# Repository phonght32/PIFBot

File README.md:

# PIFBot
  
### 1. Overview 

PIFBot is a ROS-based mobile robot for running SLAM (Simultaneous Localization and Mapping) algorithms to build a map and driving around this map. This robot is primarily equiped LiDAR, RGB-D camera and odometer sensors that makes it compatible with many SLAM methods. The PIFBot can be customized in various ways depending on how you reconstruct mechanical parts and use optional parts such as sensors and the computer to meet many different purposes. 

### 2. Requirement

#### 2.1. Ubuntu 16.04 Xenial
Ubuntu has been the primary platform for ROS. The releases is available to download from [Ubuntu home page.](https://ubuntu.com/)

#### 2.2. ROS Kinetic
This project uses ROS Kinetic that compatible with Ubuntu 16.04 (Xenial) to have better support from ROS community. Follow this [link](http://wiki.ros.org/kinetic) to see the installation instructions. 

#### 2.3. STM-IDF (STM32 Integrated Developement Framework)
[STM-IDF](https://github.com/phonght32/stm-idf) is an open source framework for STM32 that using C/C++ programming languague. The majority of the components in STM-IDF are available in [Github Repository](https://github.com/phonght32) under the MIT license. 

### 3. Mobile base control

Main controller board for PIFBot is OpenSTM32. The OpenSTM32 board is developed for ROS embedded systems to provide completely open source hardware and software. Everything about the board; Schematic, PCB Gerber, BOM and the firmware source code for PIFBot are available in [Github Repository](https://github.com/phonght32/openSTM32F4_LQFP64) and free to distribute under MIT license. 

The STM32F4 series is a main chip inside the OpenSTM32 board which is based on a very powerful ARM Cortex-M4 with Floating Point Unit (FPU). The developement environment for OpenSTM32 is wide open but STM-IDF which mentioned above is selected as main programming tool. 

OpenSTM32 provides digital and analog input/output pins that can interface with extension board or various sensors. 9-DOF IMU MPU9250 is available to make this board capable of processing complex motion fusion algorithms. OpenSTM32 features various communication interfaces: SPI, I2C, UART, I2S for other embedded devices. 

OpenSTM32 will be the best solution for implementing your embedded control design.

#### 3.1. Schematic

#### 3.2. openSTM32 Board

### 4. Hardware assembly

Differential drive which is the most common mobile robot model is applied to PIFBot. The shape of the robot is selected as circle with two driving wheels and two caster wheels. Design in this way make the robot easy to move according to control commands. 

This table shows many important size specifications of PIFBot. 

| Specification    | Dimension |
|------------------|-----------|
| Chassis diameter | 200 mm    |
| Maximum height   | 212 mm    |
| Wheel diameter   | 65 mm     |
| Axle distance    | 165 mm    |

#### 4.1. Chassis
PIFBot's chassis is made of mica. The chassis is designed in the way so that make it easy to carry optional parts as well as sensors. DXF files is available in this repository for laser cutting or CNC.

#### 4.2. Motor control and wheels
TB6560 stepper motor driver is used for controlling 42x42 mm stepper motor which working as actuator element. The PIFBot consists of two 65mm diameter fixed powered wheels mounted on the left and right side of the robot platform. Two castor wheels is used for balance and stability. 

#### 4.3. Single Board Computer
The Single Board Computer (SBC) is required to be able to install Linux ROS that provides the ability to use PIFBot's feature. There are various type of SBC, but Raspberry Pi 3 B+ is selected as main computer for PIFBot. 

#### 4.4. Controller Board
Calculating odometry data and controlling robot's motion are the essential requirements of controller board. The OpenSTM32 is designed to meet this requirements. There are also many available connectors in this board that make it suitable for various sensors or other applications. 

#### 4.5. Sensors
**RPLIDAR A1**  
360 Laser Range Finding RPLIDAR A1 is a 2D laser scanner capable of sensing 360 degrees that collects a set of data around the robot to use for SLAM (Simultaneous Localization and Mapping) and Navigation. It supportsnUSB interface and is easy to install on a PC. 

**Intel RealSense D415**  
The Intel RealSense D415 camera is a USB 3.0 device that can provide color, depth and infrared video streams. PIFBot adopts this camera to enable 3D SLAM and Navigation, and it is possible to apply various applications such as gesture recognition, object recognition and scene recognition based on 3D depth information obtained using RealSense Tecnology. 

#### 4.6. Power supply
OpenSTM32 controller board has both a 5V power and a 12V power, which are used in Raspberry Pi. DC/DC Buck Converter LM2596 is used for taking 11.1V from 3 cell lipo baterry and converting it into 5V that can power controller board and SBC.

### 5. System design

The system is seperated into two parts: ROS and base control. SBC receives data that collected from RPLIDAR A1 and Intel RealSense D415 camera to publish to ROS's topics. ROS's topics are owned by ROS Master so PC also implement publisher and subscriber to topics which contains data published from SBC. PC runs SLAM algorithms and Navigation, then publish motion commands to topic that manages robot's velocity (both angular and linear velocity). The motion command will be sent to controller board over rosserial protocol so that robot can build the map and drive around in this map. Simultaneously, controller board calculates robot's odometry data and feeds backward to ROS Server.

### 6. Result
Real-Time Appearance-Based Mapping is used for practing SLAM and Navigation. 

#### 6.1. SLAM

#### 6.2. Navigation

#### 6.3. Loop-closed detection

#### 6.4. Multi-session SLAM 

#### 6.5 Video
Follow [this link](https://youtu.be/UWhPCQyU918) to watch video on Youtube. 

#### 7. Problem
For any problems, please report to [Issues](https://github.com/phonght32/PIFBot/issues) or contact email thanhphongho1998@gmail.com

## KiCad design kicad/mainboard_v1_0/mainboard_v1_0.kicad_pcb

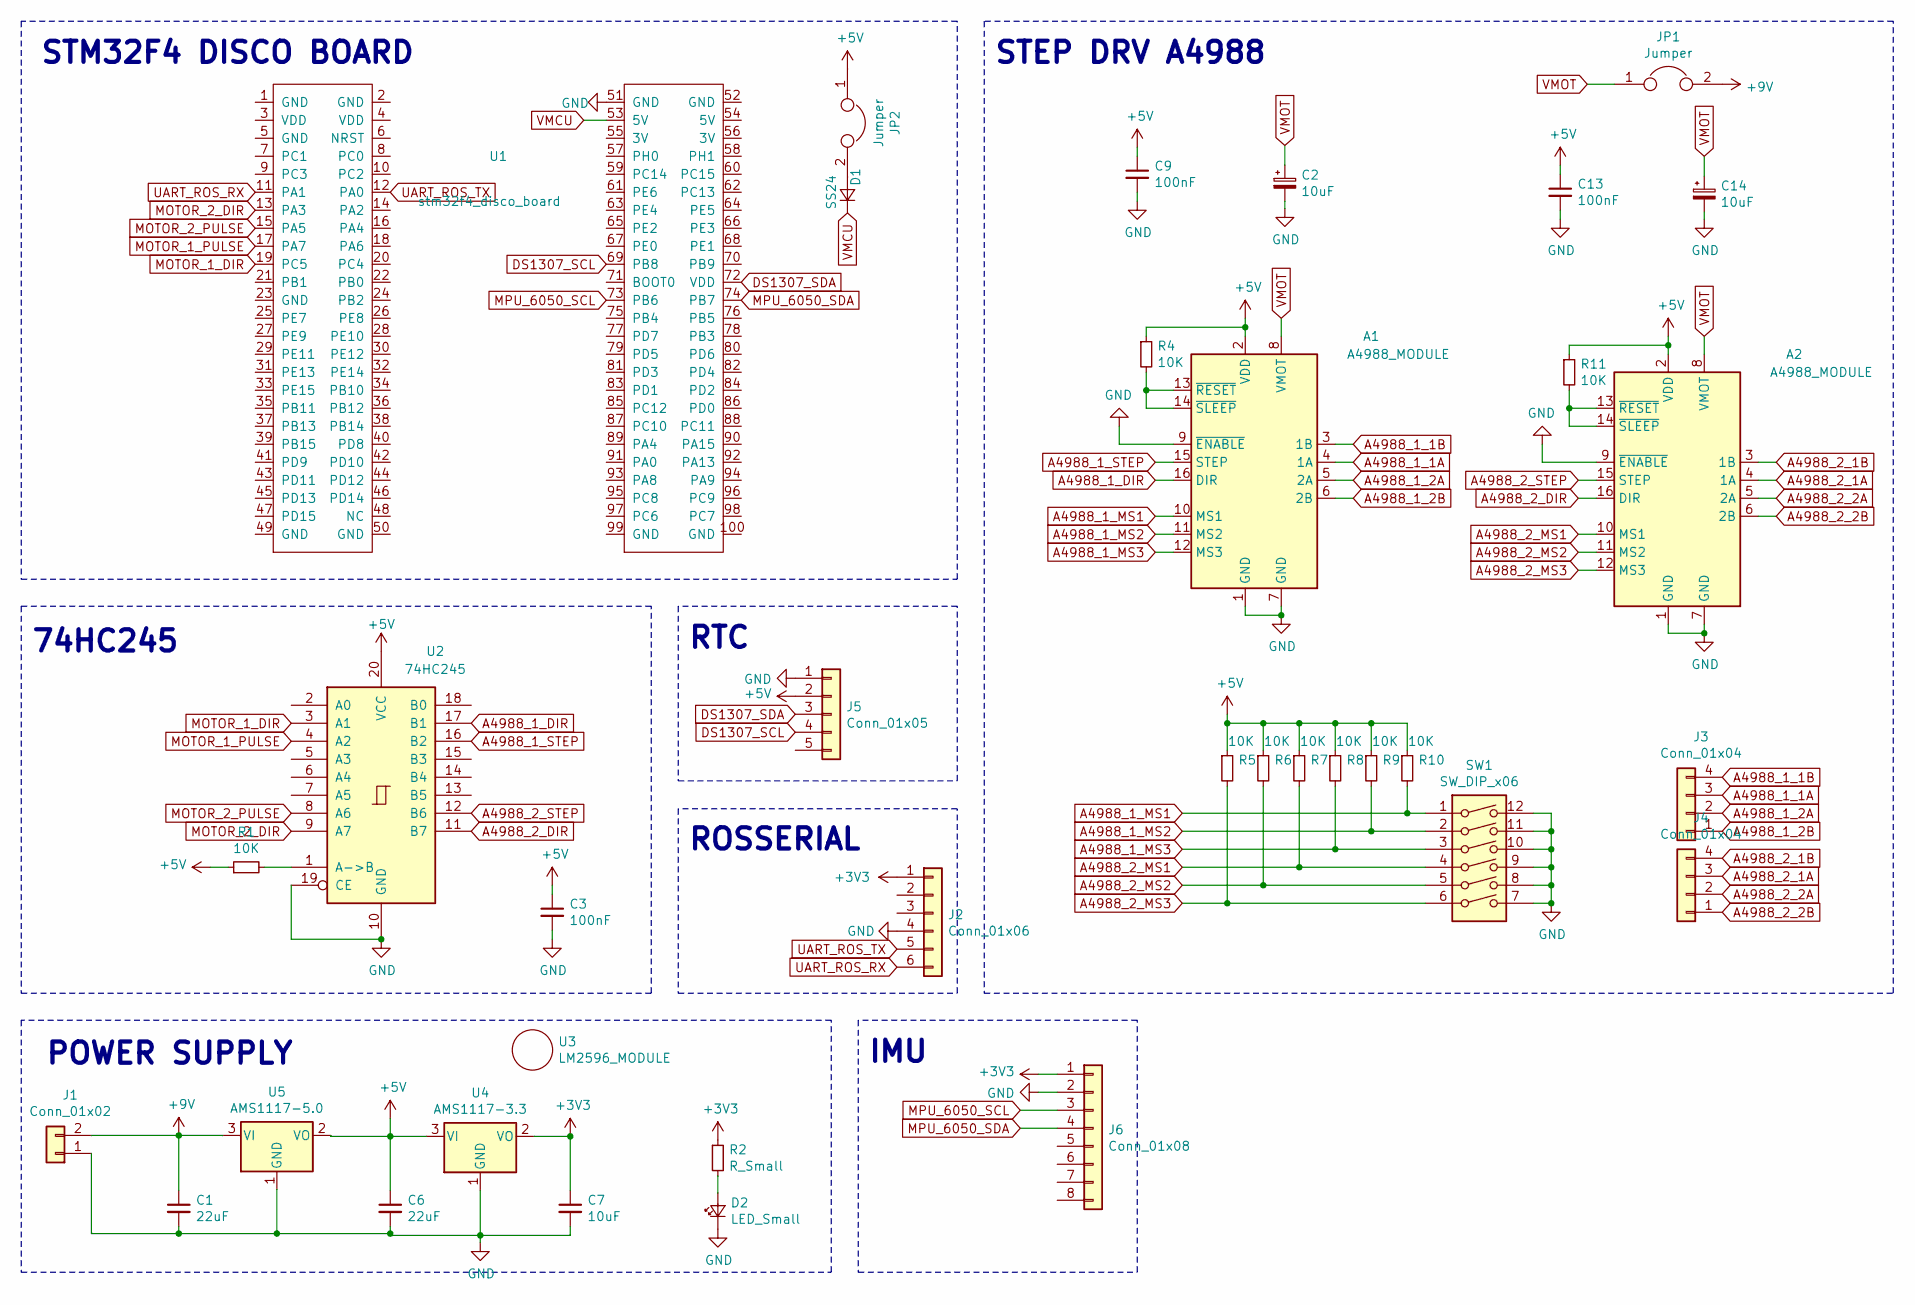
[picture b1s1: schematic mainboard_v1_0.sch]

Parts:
A1, A2: A4988_MODULE; Pololu_Breakout-16_15.2x20.3mm
C1, C6: 22uF; C_0805_2012Metric
C2, C14: 10uF; C_Radial_D8.0mm_H11.5mm_P3.50mm
C3, C9, C13: 100nF; C_0805_2012Metric
C7: 10uF; C_0805_2012Metric
D1: SS24; D_5W_P12.70mm_Horizontal
D2: LED_Small; LED_D3.0mm
J1: Conn_01x02; TerminalBlock_bornier-2_P5.08mm
J2: Conn_01x06; PinHeader_1x06_P2.54mm_Horizontal
J3, J4: Conn_01x04; PinHeader_1x04_P2.54mm_Vertical
J5: Conn_01x05; PinHeader_1x05_P2.54mm_Vertical
J6: Conn_01x08; PinHeader_1x08_P2.54mm_Vertical
JP1, JP2: Jumper; PinHeader_1x02_P2.54mm_Vertical
R1, R4, R5, R6, R7, R8, R9, R10, R11: 10K; R_Axial_DIN0207_L6.3mm_D2.5mm_P10.16mm_Horizontal
R2: R_Small; R_Axial_DIN0207_L6.3mm_D2.5mm_P10.16mm_Horizontal
SW1: SW_DIP_x06; SW_DIP_SPSTx06_Slide_9.78x17.42mm_W7.62mm_P2.54mm
U1: stm32f4_disco_board
U2: 74HC245; DIP-20_W7.62mm_LongPads
U3: LM2596_MODULE
U4: AMS1117-3.3; SOT-223-3_TabPin2
U5: AMS1117-5.0; SOT-223-3_TabPin2

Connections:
+3V3: C7.1, J2.1, J6.1, R2.1, U4.2 (VO)
+5V: A1.2 (VDD), A2.2 (VDD), C3.1, C6.1, C9.1, C13.1, J5.2, JP2.1, R1.1, R4.1, R5.1, R6.1, R7.1, R8.1, R9.1, R10.1, R11.1, U2.20 (VCC), U4.3 (VI), U5.2 (VO)
+9V: C1.1, J1.2, JP1.2, U5.3 (VI)
A4988_1_1A: A1.4 (1A), J3.3
A4988_1_1B: A1.3 (1B), J3.4
A4988_1_2A: A1.5 (2A), J3.2
A4988_1_2B: A1.6 (2B), J3.1
A4988_1_DIR: A1.16 (DIR), U2.17 (B1)
A4988_1_MS1: A1.10 (MS1), R10.2, SW1.1
A4988_1_MS2: A1.11 (MS2), R9.2, SW1.2
A4988_1_MS3: A1.12 (MS3), R8.2, SW1.3
A4988_1_STEP: A1.15 (STEP), U2.16 (B2)
A4988_2_1A: A2.4 (1A), J4.3
A4988_2_1B: A2.3 (1B), J4.4
A4988_2_2A: A2.5 (2A), J4.2
A4988_2_2B: A2.6 (2B), J4.1
A4988_2_DIR: A2.16 (DIR), U2.11 (B7)
A4988_2_MS1: A2.10 (MS1), R7.2, SW1.4
A4988_2_MS2: A2.11 (MS2), R6.2, SW1.5
A4988_2_MS3: A2.12 (MS3), R5.2, SW1.6
A4988_2_STEP: A2.15 (STEP), U2.12 (B6)
DS1307_SCL: J5.4, U1.69 (PB8)
DS1307_SDA: J5.3, U1.72 (VDD)
GND: A1.1 (GND), A1.7 (GND), A1.9 (~ENABLE), A2.1 (GND), A2.7 (GND), A2.9 (~ENABLE), C1.2, C2.2, C3.2, C6.2, C7.2, C9.2, C13.2, C14.2, D2.1 (K), J1.1, J2.4, J5.1, J6.2, SW1.7, SW1.8, SW1.9, SW1.10, SW1.11, SW1.12, U1.51 (GND), U2.10 (GND), U2.19 (CE), U4.1 (GND), U5.1 (GND)
MOTOR_1_DIR: U1.19 (PC5), U2.3 (A1)
MOTOR_1_PULSE: U1.17 (PA7), U2.4 (A2)
MOTOR_2_DIR: U1.13 (PA3), U2.9 (A7)
MOTOR_2_PULSE: U1.15 (PA5), U2.8 (A6)
MPU_6050_SCL: J6.3, U1.73 (PB6)
MPU_6050_SDA: J6.4, U1.74 (PB7)
unnamed: A1.13 (~RESET), A1.14 (~SLEEP), R4.2
unnamed: A2.13 (~RESET), A2.14 (~SLEEP), R11.2
unnamed: D1.2 (A), JP2.2
unnamed: D2.2 (A), R2.2
unnamed: R1.2, U2.1 (A->B)
UART_ROS_RX: J2.6, U1.11 (PA1)
UART_ROS_TX: J2.5, U1.12 (PA0)
VMCU: D1.1 (K), U1.53 (5V)
VMOT: A1.8 (VMOT), A2.8 (VMOT), C2.1, C14.1, JP1.1

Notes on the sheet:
STM32F4 DISCO BOARD
74HC245
POWER SUPPLY
RTC
ROSSERIAL
IMU
STEP DRV A4988

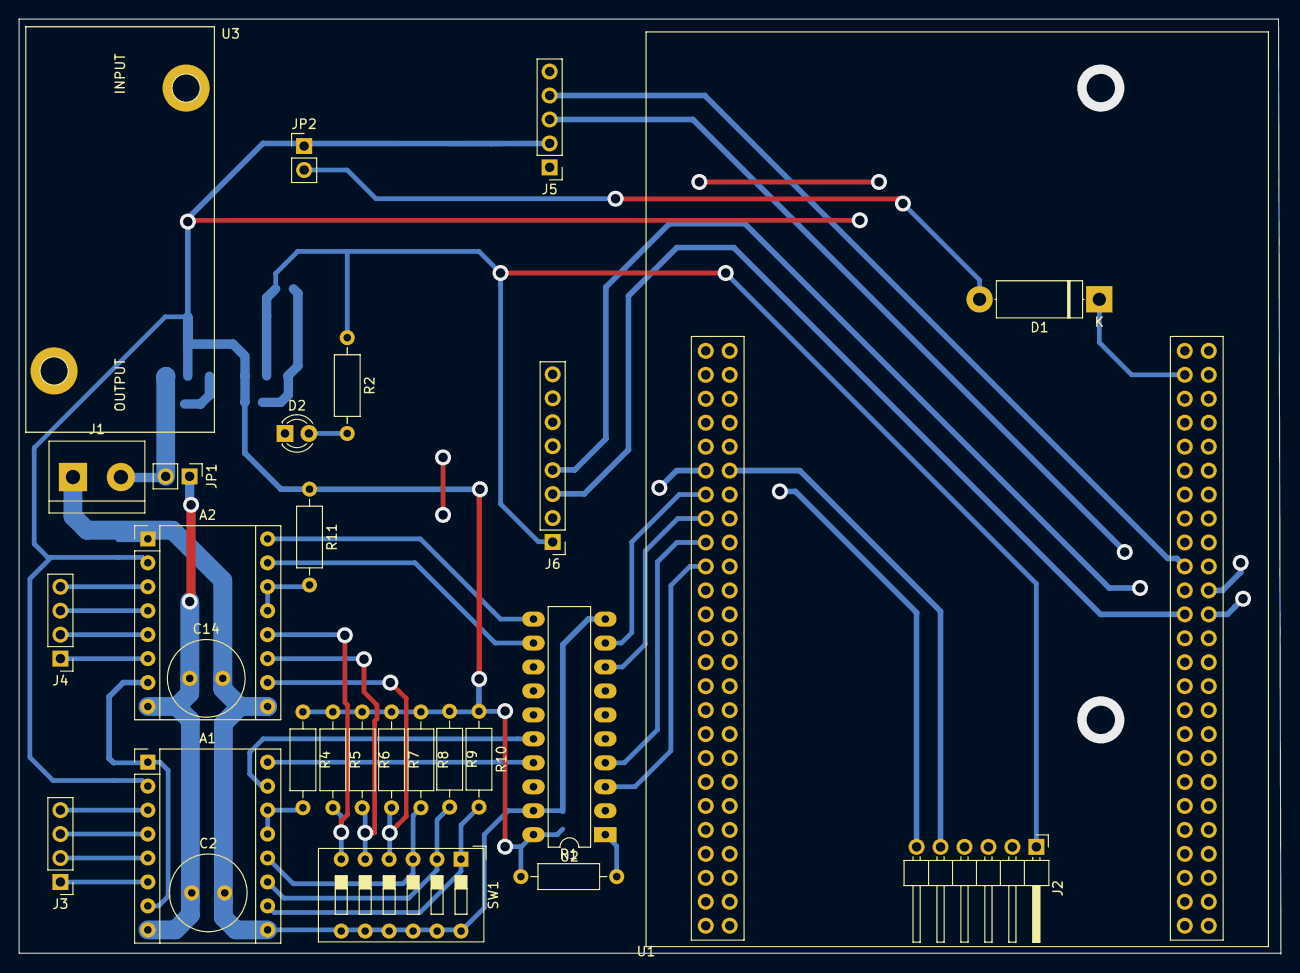
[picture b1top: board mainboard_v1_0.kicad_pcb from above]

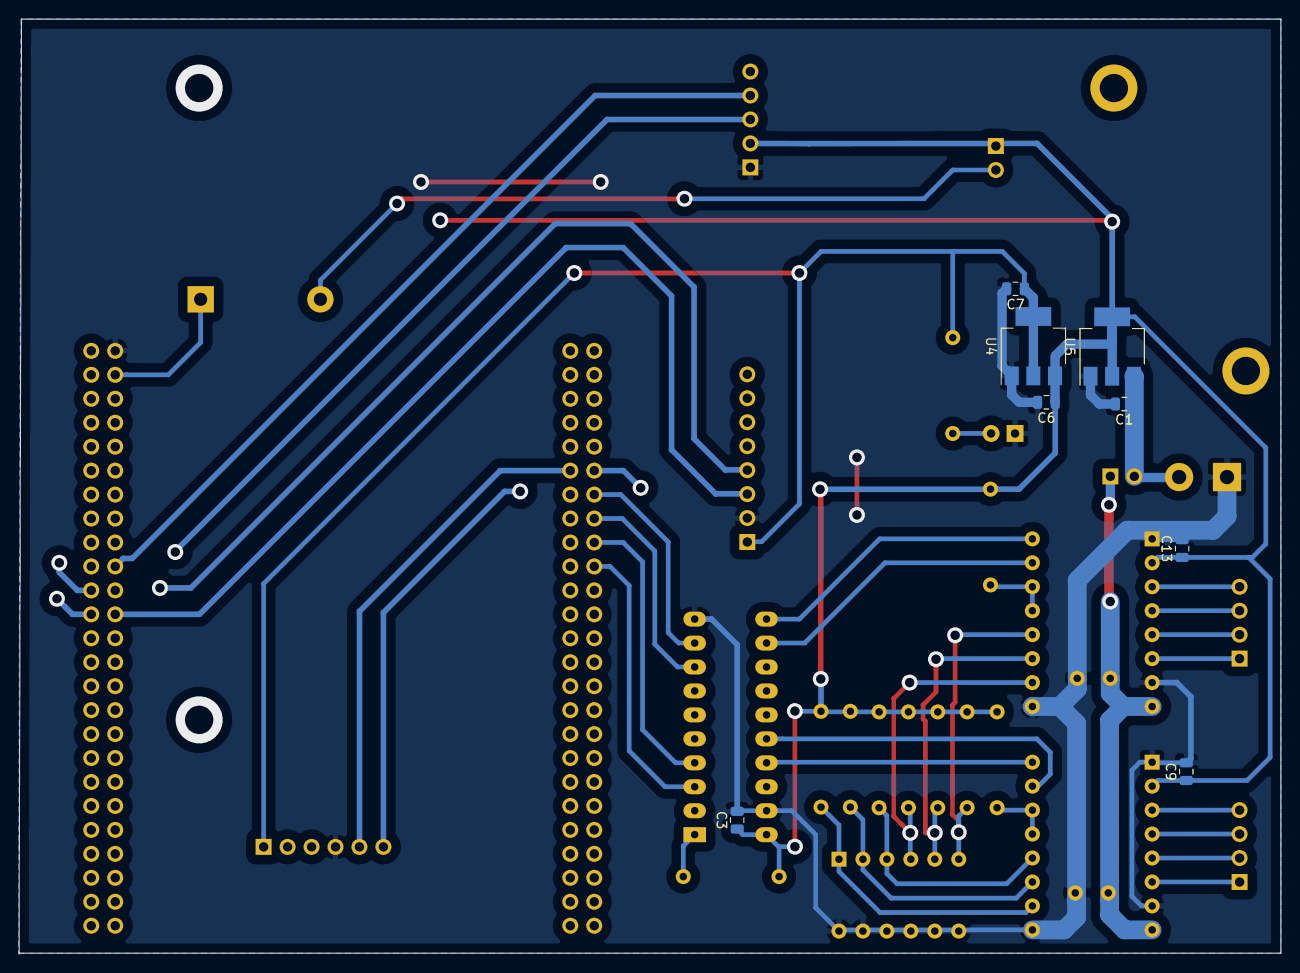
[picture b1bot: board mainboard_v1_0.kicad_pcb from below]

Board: 2 copper layers, 133.8 x 99.2 mm, 36 parts (8 on the bottom side), 39 nets.

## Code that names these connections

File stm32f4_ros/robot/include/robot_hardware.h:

/*
 * @File description:
 * 		Step motor left:
 * 			- PA5: pulse
 * 			- PA3: direction
 * 			- PE7: tick
 * 		Step motor right:
 * 			- PA7: pulse
 * 			- PC5: direction
 * 			- PE0: tick
 * 		MPU6050:
 * 			- PB8: SCL
 * 			- PB9: SDA
 * 		UART ROS:
 * 			- PA0: TXD
 * 			- PA1: RXD
 */


#ifndef _ROBOT_HARDWARE_H_
#define _ROBOT_HARDWARE_H_

#ifdef __cplusplus
extern "C" {
#endif

#include "../../stm32f4_library/driver/include/timer.h"
#include "../../stm32f4_library/driver/include/i2c.h"
#include "../../stm32f4_library/driver/include/gpio.h"
#include "../../stm32f4_library/driver/include/uart.h"
#include "../../stm32f4_library/imu/include/mpu6050.h"
#include "../../stm32f4_library/motor/include/step_motor.h"
#include "../../stm32f4_library/motor/include/encoder.h"
#include "../../stm32f4_library/imu_filter/include/imu_filter.h"



#define PI               	3.14159265359
/* Convert constant */
#define DEG2RAD(x)      (x * PI / 180.0f)     /*!< Convert from degree to radian (PI/180) */
#define RAD2DEG(x)      (x * 180.0f / PI)     /*!< convert from radian to degree (180/PI) */

/*
 * Step motor direction index.
 */
#define MOTORLEFT_FORWARD		0
#define MOTORLEFT_BACKWARD		1
#define MOTORRIGHT_FORWARD		1
#define MOTORRIGHT_BACKWARD		0

/*
 * Robot parameters
 */
#define WHEEL_RADIUS                0.033       /*!< Wheel radius in meter */
#define WHEEL_SEPARATION            0.165       /*!< Wheel separate distance in meter */
#define TURNING_RADIUS              0.08        /*!< Turning radius in degree */
#define ROBOT_RADIUS                0.1         /*!< Robot radius in meter    */

#define MAX_LINEAR_VELOCITY         (WHEEL_RADIUS * 2 * PI * 60 / 60)		/*!< Max linear velocity */
#define MAX_ANGULAR_VELOCITY        (MAX_LINEAR_VELOCITY / TURNING_RADIUS)	/*!< Max angular velocity */

#define MIN_LINEAR_VELOCITY         -MAX_LINEAR_VELOCITY					/*!< Min linear velocity */
#define MIN_ANGULAR_VELOCITY        -MAX_ANGULAR_VELOCITY					/*!< Min angular velocity */

/*
 * Step Driver Parameters.
 */
#define MICROSTEP_DIV               4			/*!< Step driver microstep divider */
#define NUM_PULSE_PER_ROUND         200			/*!< The number of pulse per round of motor */

/*
 * Robot Hardware.
 */
#define MOTORLEFT_PULSE_TIMER_NUM         	TIMER_NUM_1
#define MOTORLEFT_PULSE_TIMER_CHANNEL     	TIMER_CHANNEL_1
#define MOTORLEFT_PULSE_TIMER_PINSPACK    	TIMER_PINS_PACK_2
#define MOTORLEFT_DIR_GPIO_PORT         	GPIO_PORT_A
#define MOTORLEFT_DIR_GPIO_NUM          	GPIO_NUM_3
#define MOTORLEFT_TICK_TIMER_NUM			TIMER_NUM_2
#define MOTORLEFT_TICK_TIMER_PINSPACK		TIMER_PINS_PACK_2

#define MOTORRIGHT_PULSE_TIMER_NUM       	TIMER_NUM_14
#define MOTORRIGHT_PULSE_TIMER_CHANNEL    	TIMER_CHANNEL_1
#define MOTORRIGHT_PULSE_TIMER_PINSPACK   	TIMER_PINS_PACK_1
#define MOTORRIGHT_DIR_GPIO_PORT        	GPIO_PORT_C
#define MOTORRIGHT_DIR_GPIO_NUM         	GPIO_NUM_5
#define MOTORRIGHT_TICK_TIMER_NUM			TIMER_NUM_4
#define MOTORRIGHT_TICK_TIMER_PINSPACK		TIMER_PINS_PACK_1

#define MPU6050_I2C_NUM             		I2C_NUM_1
#define MPU6050_I2C_PINSPACK        		I2C_PINS_PACK_1

#define ROSSERIAL_BAUDRATE          		115200

/*
 * Robot Initial Function.
 */
void robot_motor_init(void);
void robot_imu_init(void);
void robot_rosserial_init(void);
void robot_encoder_init(void);

/*
 * Robot Control Motor Function.
 */
void robot_motor_left_forward(void);
void robot_motor_left_backward(void);
void robot_motor_left_set_speed(float speed);
void robot_motor_right_forward(void);
void robot_motor_right_backward(void);
void robot_motor_right_set_speed(float speed);

void robot_motor_left_start(void);
void robot_motor_left_stop(void);
void robot_motor_right_start(void);
void robot_motor_right_stop(void);

void robot_control_motor(float *goal_vel);

bool robot_motor_left_get_dir(void);
bool robot_motor_right_get_dir(void);

uint32_t robot_encoder_left_get_tick(void);
uint32_t robot_encoder_right_get_tick(void);
void robot_encoder_left_reset(void);
void robot_encoder_right_reset(void);

void robot_imu_update_quat(void);
void robot_imu_get_quat(float *quat);
void robot_imu_get_accel(float *accel);
void robot_imu_get_gyro(float *gyro);



#ifdef __cplusplus
}
#endif

#endif /* _ROBOT_HARDWARE_H_ */

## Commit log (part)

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2019-12-11 add rcc component
2019-12-11 add pwm_set_freq function
2019-12-11 add APB clock source mapping table
2019-12-11 update pwm_set_freq function
2019-12-11 update pwm_init return value
2019-12-11 add a4988_toggle_dir
2019-12-11 add a4988_set_freq
2019-12-11 change pwm init struct parameters
2019-12-11 update pwm_handle structure
2019-12-11 remove pwm set period and prescaler function
2019-12-11 change init & handle structure parameters
2019-12-11 update a4988_cleanup
2019-12-11 add status driver in a4988 handle structure
2019-12-11 remove pwm set period & prescaler
2019-12-11 fix a4988 handle structure
2019-12-11 update a4988 toggle dir
2019-12-16 add kicad component
2019-12-16 remove kicad mainboard project
2019-12-16 add gazebo
2019-12-16 update 3d model
2019-12-17 update kicad project
2019-12-18 update robot model
2019-12-18 add turtlebot3
2019-12-18 update model urdf
2019-12-18 add robot teleop
2019-12-18 add gazebo_rviz
2019-12-18 remove param robot model
2019-12-18 add slam component
2019-12-19 add robot navigation pkg
2019-12-21 complete pcb
2019-12-23 update ros
2019-12-24 change ros-stm32 hardware hea header
2019-12-24 fix stm rosserial
2019-12-25 add stm32f4 hal custom lib
2019-12-25 add uart component
2019-12-25 update check error
2019-12-26 add gpio component
2019-12-26 add dma_uart
2019-12-28 add stm32f4 ros
2019-12-28 update ac6 projec setting (path to ros_lib
2019-12-28 add custom library
2019-12-28 update uart init ros
2019-12-28 update rplidar to run robot_core
2019-12-30 update timer pwm init function
2019-12-31 update uart mapping
2019-12-31 update uart check error
2019-12-31 fix indent
2020-01-02 add i2c component
2020-01-03 add mpu6050 component
2020-01-03 add test mpu6050
2020-01-03 add stm32f4 project
2020-01-04 add step driver component
2020-01-04 update stm32f4_hal_ros
2020-01-06 add ros function callback
2020-01-07 add ros time now
2020-01-09 update robot ros function
2020-01-09 update file format
2020-01-09 add describtion
2020-01-09 add diode & led status
2020-01-13 update schematic
2020-01-13 add robot_hardware.h
2020-01-19 update mpu6050 component
2020-01-19 fix hardware
2020-01-20 remove ros/build & ros/devel
2020-01-20 update serial Port
2020-01-22 remove ros/build ros/devel folder
2020-01-30 update mpu6050 ahrs
2020-02-01 update ros diagnose
2020-02-05 remove lds driver
2020-02-05 update mpu6050 auto calib
2020-02-05 update rosserial baudrate
2020-02-05 add .gitmodules file
2020-02-05 remove rplidar package old
2020-02-08 update robot_base model
2020-02-08 update urdf description
2020-02-10 add i2c description
2020-02-10 change stm32 component folder name
2020-02-10 change stm32 component imu folder name
2020-02-10 change step_driver name
2020-02-10 change step_driver to step_motor
2020-02-10 update gitmodule
2020-02-10 update project setting
2020-02-10 remove stm32f4-library module
2020-02-10 update include path
2020-02-10 change component folder name
2020-02-10 add stm32f4_library submodule
2020-02-10 remove stm32f4 project
2020-02-10 remove ros_lib submodule in stm32f4
2020-02-10 add kicad mainboard v2.0
2020-02-10 add project file
2020-02-10 add gitignore
2020-02-11 add stm32f405
2020-02-11 update firmware
2020-02-11 update pcb object
2020-02-12 change rosserial baudrate
2020-02-12 update project settings
2020-02-12 update stm32f4_library submodule
2020-02-12 update project indent
2020-02-12 update stm32f4_libary submodule
2020-02-13 update stm32f4_library
2020-02-13 update file description and code indent
2020-02-19 update stm32 library
2020-02-25 add slam algorithm launch file
2020-02-25 change rosserial uart baudrate
2020-02-25 add encoder tick control
2020-02-25 update tick to radian convert value
2020-02-25 pull step motor tick control
2020-02-28 add encoder component
2020-02-29 fix file include
2020-02-29 update robot control motor function
2020-02-29 update control motor tick
2020-03-01 fix get imu quaternion
2020-03-01 add fpu preprocessor
2020-03-01 add initIMUcovarience function
2020-03-01 update robot configure hardware
2020-03-01 update mpu6050 get data function
2020-03-01 complete firmware enough to run
2020-03-06 change imu function name
2020-03-06 update main
2020-03-08 update imu filter and fix imu sensor function
2020-03-08 update new imu control function
2020-03-12 update MadwickAHRS sample frequency
2020-03-12 add project path to stm log component
2020-03-12 fix include path in stm log component
2020-03-17 add limo package submodule
2020-03-17 change PLUGINLIB_DECLARE_CLASS(is deprecated) to PLUGINLIB_EXPORT_CLASS
2020-03-17 remove include MrtParamGenerator
2020-03-17 update gitignore
2020-03-17 create src folder before build
2020-03-17 add src folder
2020-03-20 add combine lidar & camera submodule
2020-03-20 remove lidar-camera submodule
2020-03-20 remove submodule
2020-03-20 remove submodule file
2020-03-21 add laserscan to pointcloud package
2020-03-21 remove usb_cam submodule
2020-03-22 add limo launch file
2020-03-22 update lidar frame id argument
2020-03-22 add rviz for limo
2020-03-23 remove lidar submodule
2020-03-23 remove laserscan to pointcloud
2020-03-23 add laserscan to pointcloud submodule
2020-03-23 remove src folder
2020-03-23 add robot limo package
2020-03-23 add camera simulation
2020-03-23 create limo launch file
2020-03-26 add camerrgb & gray camera
2020-03-26 add feature matching launch file
2020-03-26 add robot limo launch file
2020-03-26 add rviz file
2020-03-26 add param file
2020-04-02 remove limo package
2020-04-02 remove robot_limo
2020-04-02 remove limo launch file
2020-04-02 change publish state frequency
2020-04-02 change robot footprint
2020-04-02 fix collision in urdf description
2020-04-10 add firmware based on stm-idf
2020-04-10 add robot_hardware
2020-04-10 add motor init
2020-04-10 add imu init
2020-04-10 add init resolver
2020-04-10 add init i2c
2020-04-10 add madgwick filter
2020-04-10 add define madwick parameters
2020-04-10 add motor control function
2020-04-10 check handle structure is empty
2020-04-10 add start motor default
2020-04-10 start resolver default
2020-04-10 add imu analysis data function
2020-04-10 add return value int config encoder function
2020-04-10 add firmware utils
2020-04-10 add robot config ros
2020-04-10 change robot utils file
2020-04-10 add include path
2020-04-10 add define parameters
2020-04-10 add ros control function
2020-04-10 change robot config file name
2020-04-10 move system clock config function into robot hardware
2020-04-10 add get motor tick function
2020-04-12 remove timer interval and use RTOS time
2020-04-12 update pwm component
2020-04-12 add example
2020-04-12 fix error cannot run imu
2020-04-12 change board name when output log
2020-04-13 add hector slam
2020-04-13 update hector slam
2020-04-13 add karto slam
2020-04-13 change param file name
2020-04-14 update control motor
2020-04-14 add example imu and motor
2020-04-14 add exploration
2020-04-14 change hector slam to default
2020-04-16 change madgwick sample rate
2020-04-16 change topic handler frequency
2020-04-16 add log output
2020-04-16 fix error when compile
2020-04-21 update stm-idf
2020-04-21 update firmware to compatible with auto startup function
2020-04-21 remove init imu covariance function
2020-04-21 remove stm32 firmware used sw4stm32
2020-04-21 remove submodule stm32f4_library
2020-04-21 remove kicad submodule
2020-04-21 remove hardware v2.0 folder
2020-04-21 fix resolver handler
2020-04-21 add hardware kicad
2020-04-21 update navigation parameters
2020-04-24 remove stm-idf component
2020-04-24 remove stm-idf
2020-04-24 add stm32f4-idf submodule and components
2020-04-24 fix error when change idf library name
2020-04-25 update imu component
2020-04-25 make robot move forward only
2020-04-25 increase time transform tolerance
2020-04-26 update costmap param
2020-04-26 change gmapping params
2020-04-26 add prometheus frontier explorer
2020-04-26 update examples
2020-04-26 remove limo rviz file
2020-04-26 remove explorer relative file
2020-04-26 add robot_explorer package
2020-04-26 fix build package depend
2020-04-26 change robot simulation folder name
2020-04-27 fix error when update timer macros
2020-04-28 add check error and input conditions
2020-05-01 add robot world simulation
2020-05-01 add ros machine learning
2020-05-01 add dqn
2020-05-02 update gazebo sim path of models
2020-05-02 update description
2020-05-02 change start position
2020-05-02 fix error state size
2020-05-02 change plugin name
2020-05-02 update train model
2020-05-02 add camera
2020-05-02 change image topic name
2020-05-03 add 2 mono camera
2020-05-03 add model collision
2020-05-03 update body collision
2020-05-03 update CMakeLists
2020-05-04 change camera topics
2020-05-04 change camera position
2020-05-04 add house simulation
2020-05-05 add stereo camera
2020-05-05 add rtabmap
2020-05-06 remove stereo visual
2020-05-07 add camera optical frames
2020-05-07 update rtabmap
2020-05-07 remove smoother cmd_vel topic
2020-05-07 add monodepth launch file
2020-05-07 add openSTM32F4 board
2020-05-07 remove old board hardware
2020-05-07 add stm32f4 base control firmware
2020-05-07 remove old firmware submodule
2020-05-07 remove old firmware project
2020-05-07 slam and navigatio packages
2020-05-07 add robot ros packages
2020-05-07 remove old ros packages
2020-05-07 remove rplidar packages
2020-05-07 rename folder mechanical
2020-05-08 add freecad lib
2020-05-08 add assets
2020-05-08 update library
2020-05-09 update assembly
2020-05-12 update raspberry pi color
2020-05-12 update extension hole
2020-05-12 update lib
2020-05-12 complete mechanical
2020-05-13 add i2c interface parameter
2020-05-14 remove stm32f4 base control
2020-05-14 add stm32 base control
2020-05-14 add stm-idf examples
2020-05-18 add render
2020-05-18 add gerber
2020-05-18 add caster front
2020-05-18 update rviz
2020-05-19 update imu
2020-05-19 add test stereo with 2 mono camera
2020-05-19 remove pov render
2020-05-19 update layer2
2020-05-19 update robot description
2020-05-22 add camera intel realsense d415
2020-05-22 add camera holder
2020-05-22 change lidar and camera hole position
2020-05-22 update dxf file
2020-05-22 create 2d shape to export dxf
2020-05-23 update robot visual
2020-05-23 update freecad library
2020-05-23 add assembly
2020-05-23 remove unused assembly file
2020-05-25 update render
2020-05-25 update export dxf file
2020-05-29 add stm32f405rg target to use openSTM32 board
2020-05-29 add board description
2020-05-29 remove fake stereo
2020-05-29 add rtabmap package
2020-06-01 update robot firmware
2020-06-01 update mpu9250 footprint
2020-06-01 update example
2020-06-01 change file name and directory
2020-06-01 fix error when set pwm frequency equal zero
2020-06-03 udpate rtabmap
2020-06-03 update motor hardware
2020-06-04 run rtabmap basic (only depth camera, without odom and lidar
2020-06-04 subscribe to /odom topic instead of using attach odom_frame_id
2020-06-05 add enable_camera param
2020-06-05 change enable_camera param name
2020-06-05 change motor step divider
2020-06-07 fix error when moving robot but rtab's pointcloud not update
2020-06-07 fix odometry error when motor tick overflow
2020-06-08 config magnetic sensor (but not use
2020-06-09 update struct data
2020-06-10 change rosserial baudrate to 912600
2020-06-11 change name of struct config
2020-06-11 change name of config functions to init functions
2020-06-14 remove openni process
2020-06-14 change rosserial baudrate to 115200
2020-06-14 remove approx_sync param
2020-06-15 remove log debug
2020-06-15 remove unused params
2020-06-18 remove openSTM32 hardware
2020-06-18 change hardware folder
2020-06-18 remove stm32 base control submodule
2020-06-18 change firmware folder
2020-06-22 add documents
2020-06-22 update new submodule
2020-06-22 add firmware submodule
2020-06-29 fix error when set pwm frequency of step motor
2020-06-29 update pwm functions in stm-idf
2020-07-07 remove documents
2020-07-19 update hardware
2020-07-19 remove unused file in mechanical
2020-08-17 update firmware tutorial
2020-08-20 add demo image folder
2021-11-29 update demo pictures
2023-01-12 update paths
2023-01-12 update submodules to latest version
2023-01-12 update submodule to latest version
